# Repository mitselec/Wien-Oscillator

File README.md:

# Wien-Oscillator
Simulation and implementation of a Wien Oscillator

This is a circuit that I simulated and implemented back in 2013.
The initial Design was made in DesignSpark, current version was made in Eagle.

Simulation was made on OrCad 9.2

Dimopoulos Dimitris 2013-2019

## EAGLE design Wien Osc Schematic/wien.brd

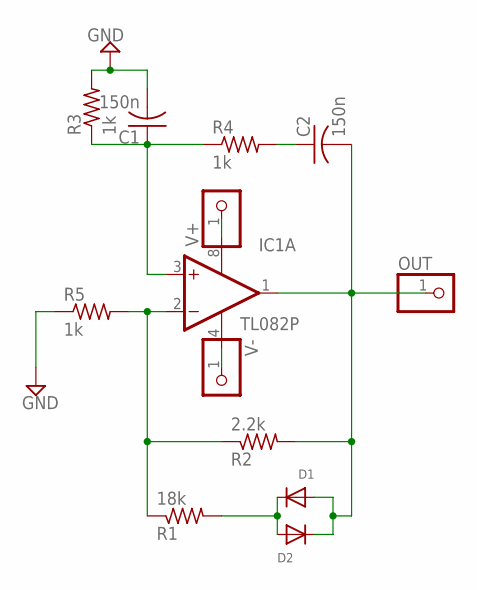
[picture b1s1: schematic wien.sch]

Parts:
C1, C2: 150n; C025-030X050
D1: DIODEDO-1N4148; DO-1N4148
D2: DO-1N4148
IC1: TL082P; DIL08
OUT: PINHD-1X1CB; 1X01-CLEANBIG
R1: 18k; 0207/12
R2: 2.2k; 0207/12
R3, R4, R5: 1k; 0207/12
V+: PINHD-1X1CB; 1X01-CLEANBIG
V-: PINHD-1X1CB; 1X01-CLEANBIG

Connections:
GND: C1.2, R3.2, R5.1
unnamed: C1.1, IC1.3 (+IN), R3.1, R4.1
unnamed: C2.1, R4.2
unnamed: IC1.8 (V+), V+.1
unnamed: IC1.4 (V-), V-.1
unnamed: IC1.2 (-IN), R1.1, R2.1, R5.2
unnamed: D1.C, D2.A, R1.2
OUT: C2.2, D1.A, D2.C, IC1.1 (OUT), OUT.1, R2.2

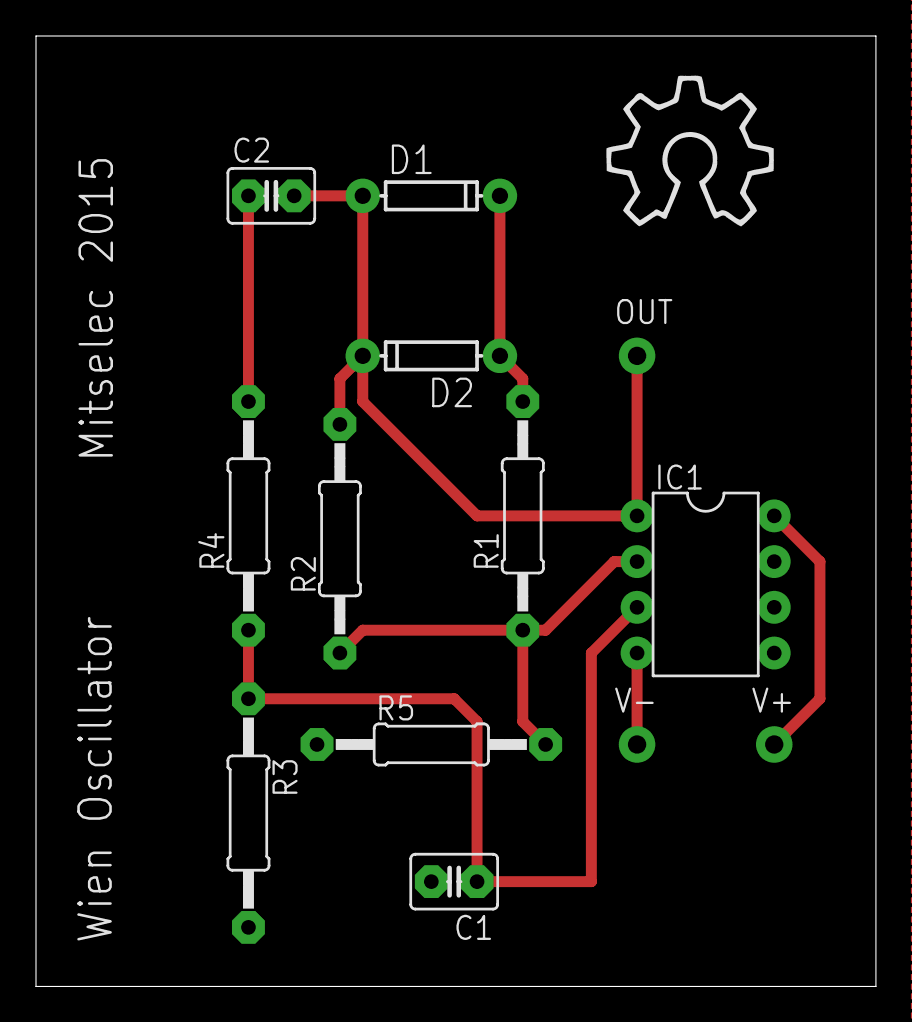
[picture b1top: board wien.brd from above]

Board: 2 copper layers, 46.7 x 52.8 mm, 13 parts (0 on the bottom side), 8 nets.
